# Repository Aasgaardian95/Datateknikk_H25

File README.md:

## Marius Aasgaard sin personlige GitHub

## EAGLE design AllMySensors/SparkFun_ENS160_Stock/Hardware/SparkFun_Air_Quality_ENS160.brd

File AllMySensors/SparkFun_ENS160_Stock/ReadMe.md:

SparkFun Indoor Air Quality Sensor - ENS160
========================================

[*SparkFun Indoor Air Quality Sensor-ENS160 (SEN-20844)*](https://www.sparkfun.com/products/20844)

The SparkFun ENS160 Indoor Air Quality Sensor is a digital multi-gas sensor solution with four sensor elements that can be used in a wide range of applications including building automation, smart home, and HVAC. The independent hotplate control allows the detection of volatile organic compounds (VOCs) including ethanol, toluene, hydrogen, and oxidizing gases with superior sensitivity. The ENS160 supports intelligent algorithms to process raw sensor measurements on-chip. These algorithms calculate CO2-equivalents, TVOC, air quality indices (AQIs), and perform humidity and temperature compensation, as well as baseline management, all on-chip. Raw sensor measurements can be read for further customization. 

The ENS160 from ScioSense is a digital multi-gas sensor consisting of four independent heaters and gas sensor elements based on metal oxide (MOX) technology and a controller. TrueVOC® air quality detection provides outputs such as eCO2, TVOC, and AQI in compliance with worldwide IAQ standards.

Along with the plug-and-play Qwiic connectors, both I<sup>2</sup>C and SPI functionality have been broken out to 0.1"-spaced pins in case you prefer to use a breadboard. 

**Note:** The default I<sup>2</sup>C address of the ENS160 is 0x53 and is jumper selectable to 0x52. 

Repository Contents
-------------------

* **/Documentation** - Data sheets, additional product information
* **/Hardware** - Eagle design files (.brd, .sch)
* **/Production** - Production panel files (.brd)

Documentation
--------------

* **[Fritzing Part](https://github.com/sparkfun/Fritzing_Parts/blob/main/products/20844_sfe_indoor_air_quality_sensor_ens160_qwiic_eco2_tvoc_aqi.fzpz)** - Fritzing part for the SparkFun Indoor Air Quality Sensor - ENS160.
* **[Library](https://github.com/sparkfun/SparkFun_Indoor_Air_Quality_Sensor-ENS160_Arduino_Library)** - Arduino library for the SparkFun Indoor Air Quality Sensor - ENS160.
* **[Hookup Guide](https://learn.sparkfun.com/tutorials/sparkfun-indoor-air-quality-sensor---ens160-qwiic-hookup-guide)** - Basic hookup guide for the SparkFun Indoor Air Quality Sensor - ENS160.

Product Versions
----------------
* [SEN-20844](https://www.sparkfun.com/products/20844) - v1.0

Version History
---------------
* v1.0 - Initial Release

License Information
-------------------

This product is _**open source**_! 

Please review the LICENSE.md file for license information. 

If you have any questions or concerns on licensing, please contact technical support on our [SparkFun forums](https://forum.sparkfun.com/viewforum.php?f=152).

Distributed as-is; no warranty is given.

- Your friends at SparkFun.

_<COLLABORATION CREDIT>_

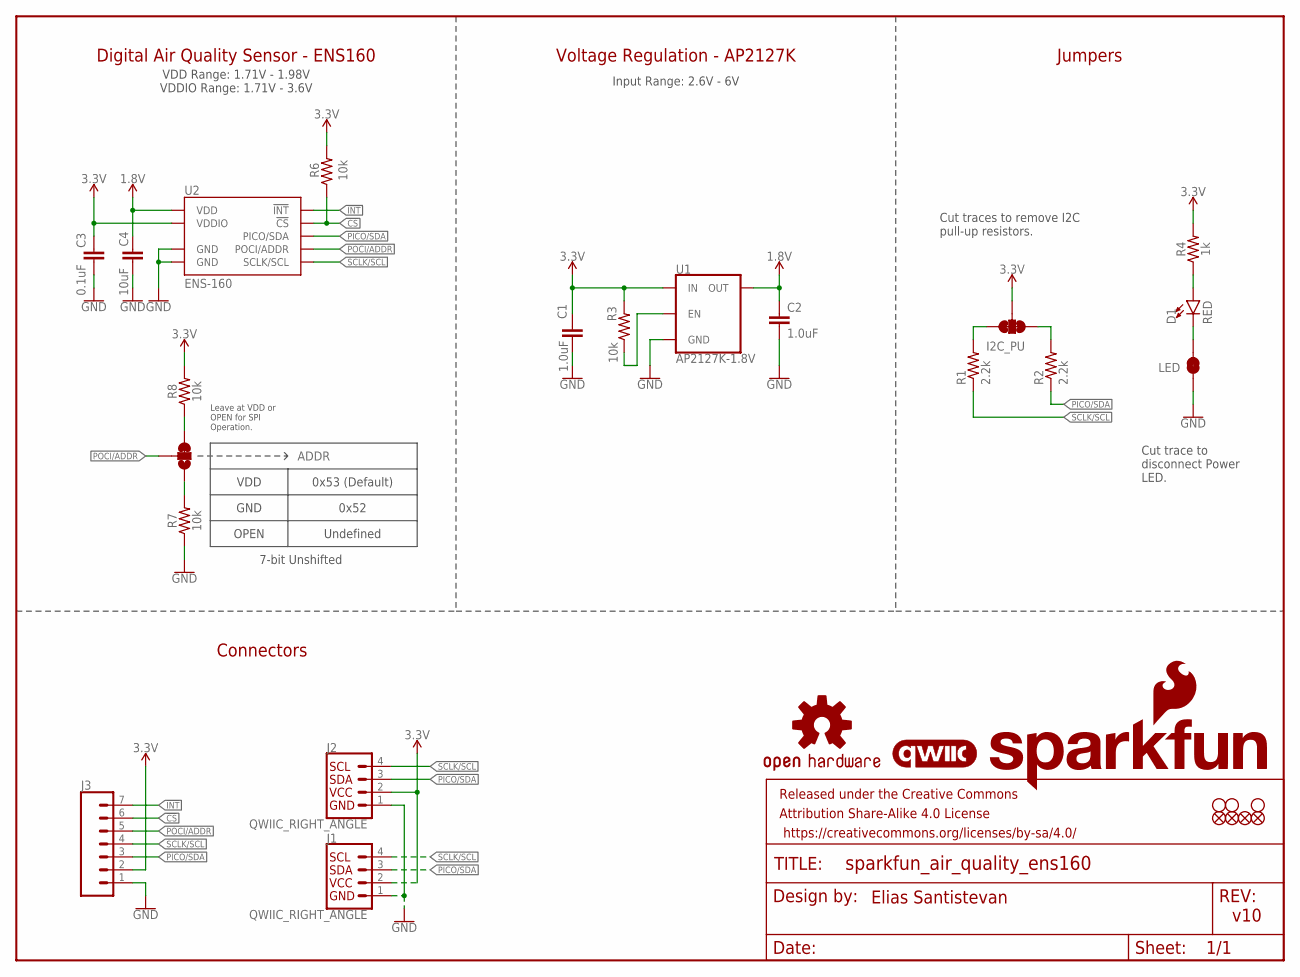
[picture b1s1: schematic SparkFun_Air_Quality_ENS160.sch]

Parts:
ADDR: JUMPER-SMT_3_1-NC_TRACE_SILK; SMT-JUMPER_3_1-NC_TRACE_SILK
C1, C2: 1.0uF; 0603
C3: 0.1uF; 0603
C4: 10uF; 0603
D1: RED; LED-0603
FD1, FD2, FD3, FD4: FIDUCIAL1X2; FIDUCIAL-1X2
FRAME1: FRAME-LETTER; CREATIVE_COMMONS
I2C_PU: S_MODE; SMT-JUMPER_3_2-NC_TRACE_SILK
J1, J2: QWIIC_RIGHT_ANGLE; JST04_1MM_RA
J3: CONN_07NO_SILK; 1X07_NO_SILK
LED: JUMPER-SMT_2_NC_TRACE_SILK; SMT-JUMPER_2_NC_TRACE_SILK
LOGO2: OSHW-LOGOMINI; OSHW-LOGO-MINI
LOGO3: SFE_LOGO_NAME_FLAME.1_INCH; SFE_LOGO_NAME_FLAME_.1
LOGO4: QWIIC_LOGO_4MM; QWIIC_4MM
R1, R2: 2.2k; 0603
R3, R6, R7, R8: 10k; 0603
R4: 1k; 0603
STANDOFF1, STANDOFF2, STANDOFF5: STAND-OFFTIGHT; STAND-OFF-TIGHT
U1: AP2127K-1.8V; SOT23-5
U2: ENS-160; LGA-9

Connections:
1.8V: C2.1, C4.1, U1.5 (OUT), U2.P4 (VDD)
3.3V: C1.1, C3.1, I2C_PU.2, J1.2, J2.2, J3.2, R3.2, R4.2, R6.2, R8.2, U1.1 (IN), U2.P5 (VDDIO)
!CS!: J3.6, R6.1, U2.P7 (!CS!)
!INT!: J3.7, U2.P6 (!INT!)
GND: C1.2, C2.2, C3.2, C4.2, J1.1, J2.1, J3.1, LED.1, R7.1, U1.2 (GND), U2.P8 (GND), U2.P9 (GND)
unnamed: R3.1, U1.3 (EN)
unnamed: D1.A, R4.1
unnamed: D1.C, LED.2
unnamed: ADDR.3, R8.1
unnamed: I2C_PU.1, R1.2
unnamed: I2C_PU.3, R2.2
unnamed: ADDR.1, R7.2
PICO/SDA: J1.3, J2.3, J3.3, R2.1, U2.P1 (PICO/SDA)
POCI/ADDR: ADDR.2, J3.5, U2.P3 (POCI/ADDR)
SCLK/SCL: J1.4, J2.4, J3.4, R1.1, U2.P2 (SCLK/SCL)

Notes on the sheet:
Cut traces to remove I2C pull-up resistors.
v10
Jumpers
Cut trace to disconnect Power LED.
Connectors
Elias Santistevan
Digital Air Quality Sensor - ENS160
VDD Range: 1.71V - 1.98V VDDIO Range: 1.71V - 3.6V
Voltage Regulation - AP2127K
VDD
GND
OPEN
0x52
0x53 (Default)
Undefined
7-bit Unshifted
Input Range: 2.6V - 6V
Leave at VDD or OPEN for SPI Operation.

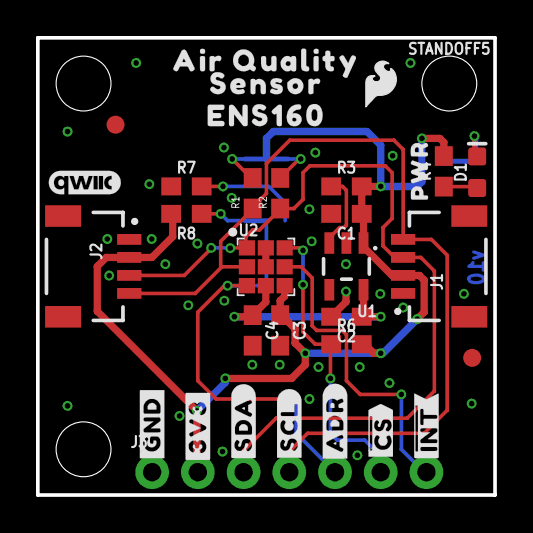
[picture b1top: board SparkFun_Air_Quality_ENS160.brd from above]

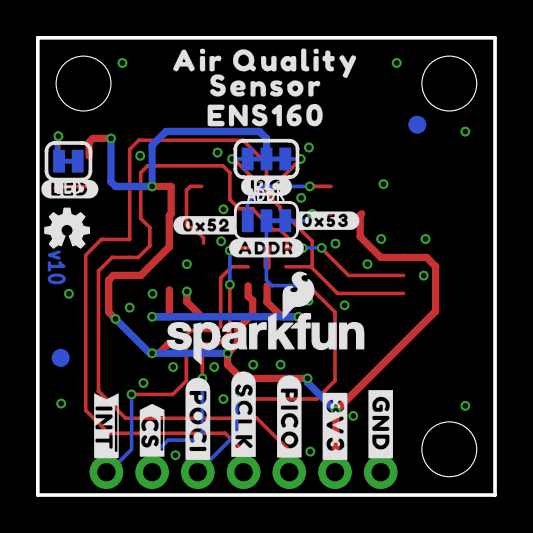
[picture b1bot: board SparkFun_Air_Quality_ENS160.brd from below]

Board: 2 copper layers, 25.4 x 25.4 mm, 58 parts (22 on the bottom side), 15 nets.

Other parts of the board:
U$1, U$9: #GND#3
U$2, U$10: #3V3#4
U$3: #SDA#5
U$4: #SCL#4
U$5, U$28: ENS16016
U$6: #ADDR#6
U$7: #SCLK#16021
U$8: #ADR#441018
U$11: ##INT##9
U$12, U$17: AIR_QUALITY441014
U$13, U$19: SENSOR441015
U$14: #0X53#16019
U$15: #0X52#16019
U$16: #LED#11
U$18: ##INT##6
U$20: SFE_LOGO_FLAME_.1
U$21: PWR9
U$22: ##CS##16019
U$23: #POCI#16020
U$24: #PICO#16021
U$25: #I2C#11
U$27: ##CS##441016

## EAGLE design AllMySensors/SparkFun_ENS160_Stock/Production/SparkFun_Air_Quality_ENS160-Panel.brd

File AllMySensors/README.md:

# Sensorbiblioteker

## Oversikt
Denne katalogen samler alle Arduino-bibliotekene som brukes i undervisningsprosjektet. Hvert bibliotek arver fra `BaseSensor` og følger samme struktur med en `src/`-mappe for kode og en `examples/`-mappe med minst ett komplett `.ino`-program. Les README-filen i hvert bibliotek for detaljert bruk, koblingsskjema og læringsmål.

## Struktur
```
.
├── BME280Sensor/
├── BaseSensor/
├── ENS160Sensor/
├── KeypadInput/
├── LDRSensor/
├── PIRSensor/
└── RFIDReader/
```

## Biblioteksliste
| Bibliotek | Formål | Eksempelfil |
| --- | --- | --- |
| `BME280Sensor` | Leser temperatur, fuktighet og trykk over I²C. | `examples/BME280Sensor_Example/BME280Sensor_Example.ino` |
| `BaseSensor` | Abstrakt grunnklasse som standardiserer `begin()`, `read()` og logging. | Brukes av alle andre biblioteker | 
| `ENS160Sensor` | Håndterer luftkvalitetssensoren ENS160 med eCO₂- og AQI-data. | `examples/ENS160Sensor_Example/ENS160Sensor_Example.ino` |
| `KeypadInput` | Leser 4x4-matrise-tastatur og leverer siste tastetrykk. | `examples/Keypad_AccessControl/Keypad_AccessControl.ino` |
| `LDRSensor` | Leser analogt lysnivå fra LDR i spenningsdeler. | `examples/LDRSensor_Example/LDRSensor_Example.ino` |
| `PIRSensor` | Registrerer bevegelse fra en PIR-sensor og styrer indikator-LED. | `examples/PIRSensor_Example/PIRSensor_Example.ino` |
| `RFIDReader` | Styrer MFRC522 RFID-leser via SPI og eksponerer kortets UID. | `examples/RFIDReader_Example/RFIDReader_Example.ino` |

## Bruk av bibliotekene
1. Kopier mappen til `Documents/Arduino/libraries/`.
2. Start Arduino IDE og åpne eksemplene fra `Fil → Eksempler → <Biblioteksnavn>`.
3. Kompiler og last opp til et kompatibelt kort (Arduino Uno, Nano o.l.).

Alle bibliotekene kan kombineres gjennom `BaseSensor`-grensesnittet for å demonstrere objektorientert design og polymorfisme.

## For undervisning
Strukturen gjør det enkelt å diskutere:
- Hvordan arv og virtuelle metoder brukes for å gi felles API til ulike sensorer.
- Forskjeller mellom analoge, digitale, I²C- og SPI-baserte sensorer.
- Hvordan komplette undervisningsopplegg kan bygges ved å kombinere flere sensorer og felles baseklasser.

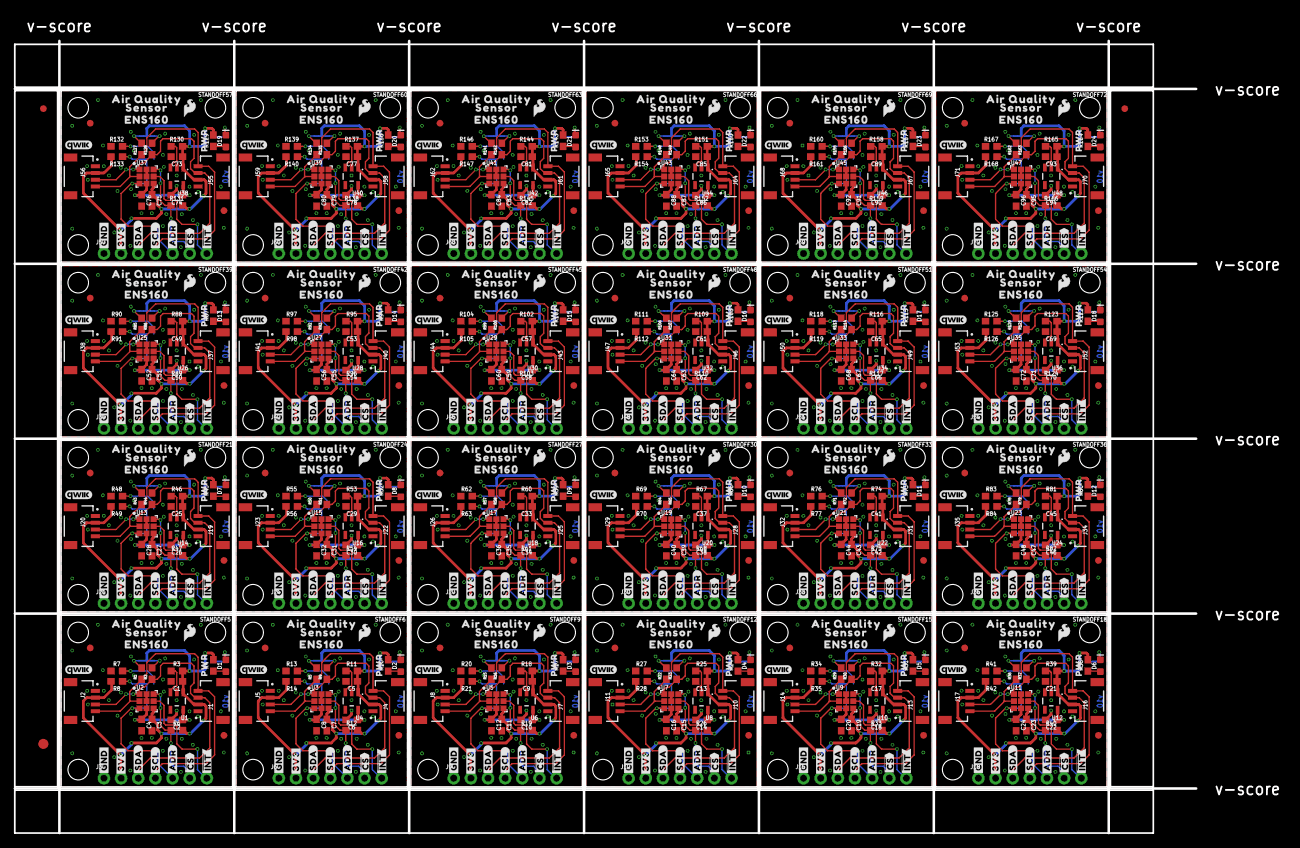
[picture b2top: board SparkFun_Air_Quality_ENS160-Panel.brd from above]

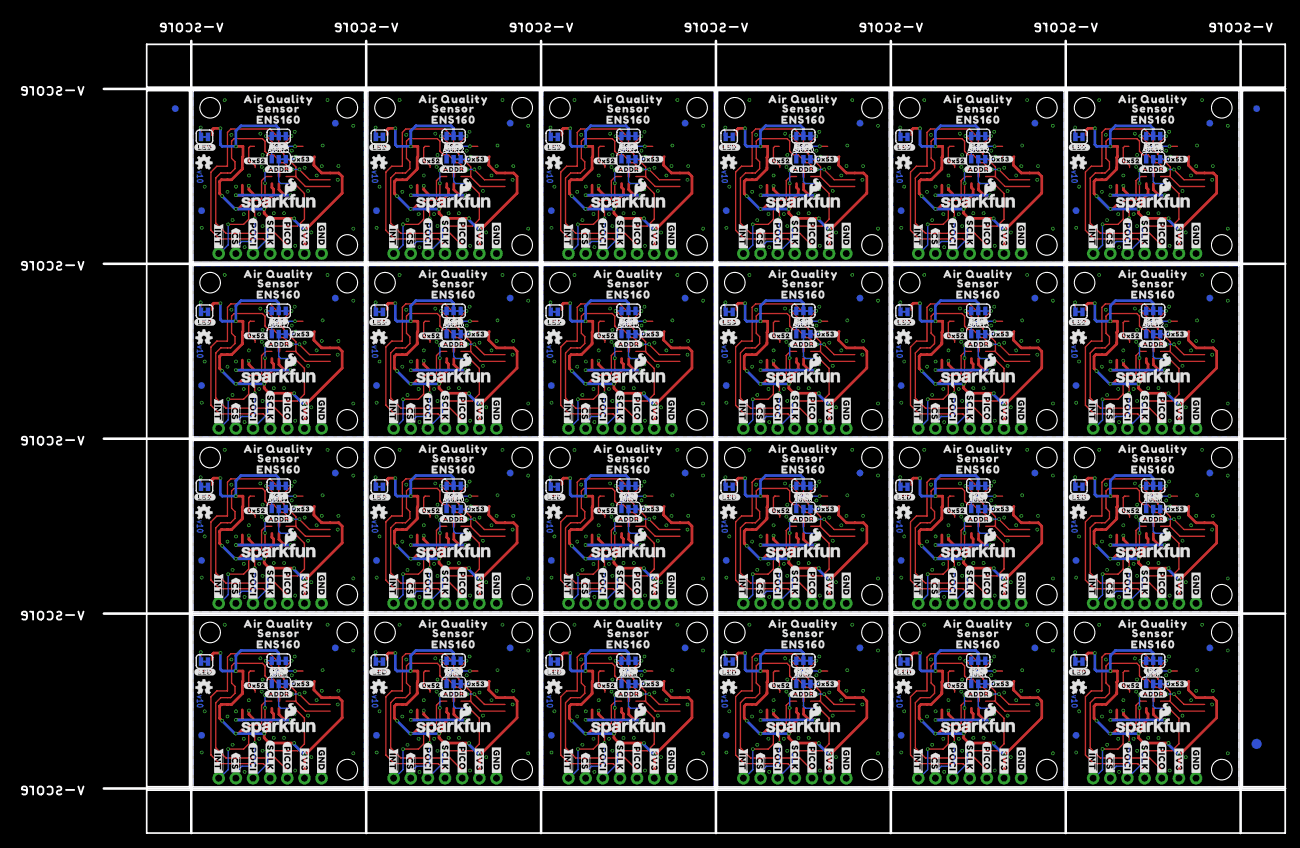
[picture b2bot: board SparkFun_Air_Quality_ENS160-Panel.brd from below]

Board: 2 copper layers, 188.2 x 121.2 mm, 1374 parts (531 on the bottom side), 360 nets.

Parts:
ADDR, ADDR1, ADDR2, ADDR3, ADDR4, ADDR5, ADDR6, ADDR7, ADDR8, ADDR9, ADDR10, ADDR11, ADDR12, ADDR13, ADDR14, ADDR15, ADDR16, ADDR17, ADDR18, ADDR19, ADDR20, ADDR21, ADDR22, ADDR23: JUMPER-SMT_3_1-NC_TRACE_SILK; SMT-JUMPER_3_1-NC_TRACE_SILK
C1, C2, C5, C6, C9, C10, C13, C14, C17, C18, C21, C22, C25, C26, C29, C30, C33, C34, C37, C38, C41, C42, C45, C46, C49, C50, C53, C54, C57, C58, C61, C62, C65, C66, C69, C70, C73, C74, C77, C78, C81, C82, C85, C86, C89, C90, C93, C94: 1.0uF; 0603
C3, C7, C11, C15, C19, C23, C27, C31, C35, C39, C43, C47, C51, C55, C59, C63, C67, C71, C75, C79, C83, C87, C91, C95: 0.1uF; 0603
C4, C8, C12, C16, C20, C24, C28, C32, C36, C40, C44, C48, C52, C56, C60, C64, C68, C72, C76, C80, C84, C88, C92, C96: 10uF; 0603
D1, D2, D3, D4, D5, D6, D7, D8, D9, D10, D11, D12, D13, D14, D15, D16, D17, D18, D19, D20, D21, D22, D23, D24: RED; LED-0603
E$1, E$2, E$3, E$4: FIDUCIAL-1X2
E$5, E$6: FIDUCIAL-1.5X3
FD1, FD2, FD3, FD4, FD5, FD6, FD7, FD8, FD9, FD10, FD11, FD12, FD13, FD14, FD15, FD16, FD17, FD18, FD19, FD20, FD21, FD22, FD23, FD24, FD25, FD26, FD27, FD28, FD29, FD30, FD31, FD32, FD33, FD34, FD35, FD36, FD37, FD38, FD39, FD40, FD41, FD42, FD43, FD44, FD45, FD46, FD47, FD48, FD49, FD50, FD51, FD52, FD53, FD54, FD55, FD56, FD57, FD58, FD59, FD60, FD61, FD62, FD63, FD64, FD65, FD66, FD67, FD68, FD69, FD70, FD71, FD72, FD73, FD74, FD75, FD76, FD77, FD78, FD79, FD80, FD81, FD82, FD83, FD84, FD85, FD86, FD87, FD88, FD89, FD90, FD91, FD92, FD93, FD94, FD95, FD96: FIDUCIAL1X2; FIDUCIAL-1X2
I2C_PU, I2C_PU1, I2C_PU2, I2C_PU3, I2C_PU4, I2C_PU5, I2C_PU6, I2C_PU7, I2C_PU8, I2C_PU9, I2C_PU10, I2C_PU11, I2C_PU12, I2C_PU13, I2C_PU14, I2C_PU15, I2C_PU16, I2C_PU17, I2C_PU18, I2C_PU19, I2C_PU20, I2C_PU21, I2C_PU22, I2C_PU23: S_MODE; SMT-JUMPER_3_2-NC_TRACE_SILK
J1, J2, J4, J5, J7, J8, J10, J11, J13, J14, J16, J17, J19, J20, J22, J23, J25, J26, J28, J29, J31, J32, J34, J35, J37, J38, J40, J41, J43, J44, J46, J47, J49, J50, J52, J53, J55, J56, J58, J59, J61, J62, J64, J65, J67, J68, J70, J71: QWIIC_RIGHT_ANGLE; JST04_1MM_RA
J3, J6, J9, J12, J15, J18, J21, J24, J27, J30, J33, J36, J39, J42, J45, J48, J51, J54, J57, J60, J63, J66, J69, J72: 1X07_NO_SILK
LED, LED1, LED2, LED3, LED4, LED5, LED6, LED7, LED8, LED9, LED10, LED11, LED12, LED13, LED14, LED15, LED16, LED17, LED18, LED19, LED20, LED21, LED22, LED23: JUMPER-SMT_2_NC_TRACE_SILK; SMT-JUMPER_2_NC_TRACE_SILK
LOGO1, LOGO2, LOGO7, LOGO10, LOGO13, LOGO16, LOGO19, LOGO22, LOGO25, LOGO28, LOGO31, LOGO34, LOGO37, LOGO40, LOGO43, LOGO46, LOGO49, LOGO52, LOGO55, LOGO58, LOGO61, LOGO64, LOGO67, LOGO70: OSHW-LOGOMINI; OSHW-LOGO-MINI
LOGO3, LOGO5, LOGO8, LOGO11, LOGO14, LOGO17, LOGO20, LOGO23, LOGO26, LOGO29, LOGO32, LOGO35, LOGO38, LOGO41, LOGO44, LOGO47, LOGO50, LOGO53, LOGO56, LOGO59, LOGO62, LOGO65, LOGO68, LOGO71: SFE_LOGO_NAME_FLAME.1_INCH; SFE_LOGO_NAME_FLAME_.1
LOGO4, LOGO6, LOGO9, LOGO12, LOGO15, LOGO18, LOGO21, LOGO24, LOGO27, LOGO30, LOGO33, LOGO36, LOGO39, LOGO42, LOGO45, LOGO48, LOGO51, LOGO54, LOGO57, LOGO60, LOGO63, LOGO66, LOGO69, LOGO72: QWIIC_LOGO_4MM; QWIIC_4MM
R1, R2, R5, R9, R15, R16, R22, R23, R29, R30, R36, R37, R43, R44, R50, R51, R57, R58, R64, R65, R71, R72, R78, R79, R85, R86, R92, R93, R99, R100, R106, R107, R113, R114, R120, R121, R127, R128, R134, R135, R141, R142, R148, R149, R155, R156, R162, R163: 2.2k; 0603
R3, R6, R7, R8, R11, R12, R13, R14, R18, R19, R20, R21, R25, R26, R27, R28, R32, R33, R34, R35, R39, R40, R41, R42, R46, R47, R48, R49, R53, R54, R55, R56, R60, R61, R62, R63, R67, R68, R69, R70, R74, R75, R76, R77, R81, R82, R83, R84, R88, R89, R90, R91, R95, R96, R97, R98, R102, R103, R104, R105, R109, R110, R111, R112, R116, R117, R118, R119, R123, R124, R125, R126, R130, R131, R132, R133, R137, R138, R139, R140, R144, R145, R146, R147, R151, R152, R153, R154, R158, R159, R160, R161, R165, R166, R167, R168: 10k; 0603
R4, R10, R17, R24, R31, R38, R45, R52, R59, R66, R73, R80, R87, R94, R101, R108, R115, R122, R129, R136, R143, R150, R157, R164: 1k; 0603
STANDOFF1, STANDOFF2, STANDOFF3, STANDOFF4, STANDOFF5, STANDOFF6, STANDOFF7, STANDOFF8, STANDOFF9, STANDOFF10, STANDOFF11, STANDOFF12, STANDOFF13, STANDOFF14, STANDOFF15, STANDOFF16, STANDOFF17, STANDOFF18, STANDOFF19, STANDOFF20, STANDOFF21, STANDOFF22, STANDOFF23, STANDOFF24, STANDOFF25, STANDOFF26, STANDOFF27, STANDOFF28, STANDOFF29, STANDOFF30, STANDOFF31, STANDOFF32, STANDOFF33, STANDOFF34, STANDOFF35, STANDOFF36, STANDOFF37, STANDOFF38, STANDOFF39, STANDOFF40, STANDOFF41, STANDOFF42, STANDOFF43, STANDOFF44, STANDOFF45, STANDOFF46, STANDOFF47, STANDOFF48, STANDOFF49, STANDOFF50, STANDOFF51, STANDOFF52, STANDOFF53, STANDOFF54, STANDOFF55, STANDOFF56, STANDOFF57, STANDOFF58, STANDOFF59, STANDOFF60, STANDOFF61, STANDOFF62, STANDOFF63, STANDOFF64, STANDOFF65, STANDOFF66, STANDOFF67, STANDOFF68, STANDOFF69, STANDOFF70, STANDOFF71, STANDOFF72: STAND-OFFTIGHT; STAND-OFF-TIGHT
U1, U4, U6, U8, U10, U12, U14, U16, U18, U20, U22, U24, U26, U28, U30, U32, U34, U36, U38, U40, U42, U44, U46, U48: AP2127K-1.8V; SOT23-5
U2, U3, U5, U7, U9, U11, U13, U15, U17, U19, U21, U23, U25, U27, U29, U31, U33, U35, U37, U39, U41, U43, U45, U47: ENS-160; LGA-9
U$1, U$9, U$30, U$34, U$57, U$61, U$84, U$88, U$111, U$115, U$138, U$142, U$165, U$169, U$192, U$196, U$219, U$223, U$246, U$250, U$273, U$277, U$300, U$304, U$327, U$331, U$354, U$358, U$381, U$385, U$408, U$412, U$435, U$439, U$462, U$466, U$489, U$493, U$516, U$520, U$543, U$547, U$570, U$574, U$597, U$601, U$624, U$628: #GND#3
U$2, U$10, U$31, U$35, U$58, U$62, U$85, U$89, U$112, U$116, U$139, U$143, U$166, U$170, U$193, U$197, U$220, U$224, U$247, U$251, U$274, U$278, U$301, U$305, U$328, U$332, U$355, U$359, U$382, U$386, U$409, U$413, U$436, U$440, U$463, U$467, U$490, U$494, U$517, U$521, U$544, U$548, U$571, U$575, U$598, U$602, U$625, U$629: #3V3#4
U$3, U$32, U$59, U$86, U$113, U$140, U$167, U$194, U$221, U$248, U$275, U$302, U$329, U$356, U$383, U$410, U$437, U$464, U$491, U$518, U$545, U$572, U$599, U$626: #SDA#5
U$4, U$33, U$60, U$87, U$114, U$141, U$168, U$195, U$222, U$249, U$276, U$303, U$330, U$357, U$384, U$411, U$438, U$465, U$492, U$519, U$546, U$573, U$600, U$627: #SCL#4
U$5, U$28, U$44, U$51, U$71, U$78, U$98, U$105, U$125, U$132, U$152, U$159, U$179, U$186, U$206, U$213, U$233, U$240, U$260, U$267, U$287, U$294, U$314, U$321, U$341, U$348, U$368, U$375, U$395, U$402, U$422, U$429, U$449, U$456, U$476, U$483, U$503, U$510, U$530, U$537, U$557, U$564, U$584, U$591, U$611, U$618, U$638, U$645: ENS16016
U$6, U$45, U$72, U$99, U$126, U$153, U$180, U$207, U$234, U$261, U$288, U$315, U$342, U$369, U$396, U$423, U$450, U$477, U$504, U$531, U$558, U$585, U$612, U$639: #ADDR#6
U$7, U$49, U$76, U$103, U$130, U$157, U$184, U$211, U$238, U$265, U$292, U$319, U$346, U$373, U$400, U$427, U$454, U$481, U$508, U$535, U$562, U$589, U$616, U$643: #SCLK#16021
U$8, U$52, U$79, U$106, U$133, U$160, U$187, U$214, U$241, U$268, U$295, U$322, U$349, U$376, U$403, U$430, U$457, U$484, U$511, U$538, U$565, U$592, U$619, U$646: #ADR#441018
U$11, U$37, U$64, U$91, U$118, U$145, U$172, U$199, U$226, U$253, U$280, U$307, U$334, U$361, U$388, U$415, U$442, U$469, U$496, U$523, U$550, U$577, U$604, U$631: ##INT##9
U$12, U$17, U$38, U$40, U$65, U$67, U$92, U$94, U$119, U$121, U$146, U$148, U$173, U$175, U$200, U$202, U$227, U$229, U$254, U$256, U$281, U$283, U$308, U$310, U$335, U$337, U$362, U$364, U$389, U$391, U$416, U$418, U$443, U$445, U$470, U$472, U$497, U$499, U$524, U$526, U$551, U$553, U$578, U$580, U$605, U$607, U$632, U$634: AIR_QUALITY441014
U$13, U$19, U$39, U$41, U$66, U$68, U$93, U$95, U$120, U$122, U$147, U$149, U$174, U$176, U$201, U$203, U$228, U$230, U$255, U$257, U$282, U$284, U$309, U$311, U$336, U$338, U$363, U$365, U$390, U$392, U$417, U$419, U$444, U$446, U$471, U$473, U$498, U$500, U$525, U$527, U$552, U$554, U$579, U$581, U$606, U$608, U$633, U$635: SENSOR441015
U$14, U$46, U$73, U$100, U$127, U$154, U$181, U$208, U$235, U$262, U$289, U$316, U$343, U$370, U$397, U$424, U$451, U$478, U$505, U$532, U$559, U$586, U$613, U$640: #0X53#16019
U$15, U$47, U$74, U$101, U$128, U$155, U$182, U$209, U$236, U$263, U$290, U$317, U$344, U$371, U$398, U$425, U$452, U$479, U$506, U$533, U$560, U$587, U$614, U$641: #0X52#16019
U$16, U$26, U$55, U$82, U$109, U$136, U$163, U$190, U$217, U$244, U$271, U$298, U$325, U$352, U$379, U$406, U$433, U$460, U$487, U$514, U$541, U$568, U$595, U$622: #LED#11
U$18, U$36, U$63, U$90, U$117, U$144, U$171, U$198, U$225, U$252, U$279, U$306, U$333, U$360, U$387, U$414, U$441, U$468, U$495, U$522, U$549, U$576, U$603, U$630: ##INT##6
U$20, U$42, U$69, U$96, U$123, U$150, U$177, U$204, U$231, U$258, U$285, U$312, U$339, U$366, U$393, U$420, U$447, U$474, U$501, U$528, U$555, U$582, U$609, U$636: SFE_LOGO_FLAME_.1
U$21, U$43, U$70, U$97, U$124, U$151, U$178, U$205, U$232, U$259, U$286, U$313, U$340, U$367, U$394, U$421, U$448, U$475, U$502, U$529, U$556, U$583, U$610, U$637: PWR9
U$22, U$48, U$75, U$102, U$129, U$156, U$183, U$210, U$237, U$264, U$291, U$318, U$345, U$372, U$399, U$426, U$453, U$480, U$507, U$534, U$561, U$588, U$615, U$642: ##CS##16019
U$23, U$53, U$80, U$107, U$134, U$161, U$188, U$215, U$242, U$269, U$296, U$323, U$350, U$377, U$404, U$431, U$458, U$485, U$512, U$539, U$566, U$593, U$620, U$647: #POCI#16020
U$24, U$54, U$81, U$108, U$135, U$162, U$189, U$216, U$243, U$270, U$297, U$324, U$351, U$378, U$405, U$432, U$459, U$486, U$513, U$540, U$567, U$594, U$621, U$648: #PICO#16021
U$25, U$29, U$56, U$83, U$110, U$137, U$164, U$191, U$218, U$245, U$272, U$299, U$326, U$353, U$380, U$407, U$434, U$461, U$488, U$515, U$542, U$569, U$596, U$623: #I2C#11
U$27, U$50, U$77, U$104, U$131, U$158, U$185, U$212, U$239, U$266, U$293, U$320, U$347, U$374, U$401, U$428, U$455, U$482, U$509, U$536, U$563, U$590, U$617, U$644: ##CS##441016

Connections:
1.8V: C2.1, C4.1, U1.5, U2.P4
1.8V1: C6.1, C8.1, U3.P4, U4.5
1.8V2: C10.1, C12.1, U5.P4, U6.5
1.8V3: C14.1, C16.1, U7.P4, U8.5
1.8V4: C18.1, C20.1, U9.P4, U10.5
1.8V5: C22.1, C24.1, U11.P4, U12.5
1.8V6: C26.1, C28.1, U13.P4, U14.5
1.8V7: C30.1, C32.1, U15.P4, U16.5
1.8V8: C34.1, C36.1, U17.P4, U18.5
1.8V9: C38.1, C40.1, U19.P4, U20.5
1.8V10: C42.1, C44.1, U21.P4, U22.5
1.8V11: C46.1, C48.1, U23.P4, U24.5
1.8V12: C50.1, C52.1, U25.P4, U26.5
1.8V13: C54.1, C56.1, U27.P4, U28.5
1.8V14: C58.1, C60.1, U29.P4, U30.5
1.8V15: C62.1, C64.1, U31.P4, U32.5
1.8V16: C66.1, C68.1, U33.P4, U34.5
1.8V17: C70.1, C72.1, U35.P4, U36.5
1.8V18: C74.1, C76.1, U37.P4, U38.5
1.8V19: C78.1, C80.1, U39.P4, U40.5
1.8V20: C82.1, C84.1, U41.P4, U42.5
1.8V21: C86.1, C88.1, U43.P4, U44.5
1.8V22: C90.1, C92.1, U45.P4, U46.5
1.8V23: C94.1, C96.1, U47.P4, U48.5
3.3V: C1.1, C3.1, I2C_PU.2, J1.2, J2.2, J3.2, R3.2, R4.2, R6.2, R8.2, U1.1, U2.P5
3.3V1: C5.1, C7.1, I2C_PU1.2, J4.2, J5.2, J6.2, R10.2, R11.2, R12.2, R14.2, U3.P5, U4.1
3.3V2: C9.1, C11.1, I2C_PU2.2, J7.2, J8.2, J9.2, R17.2, R18.2, R19.2, R21.2, U5.P5, U6.1
3.3V3: C13.1, C15.1, I2C_PU3.2, J10.2, J11.2, J12.2, R24.2, R25.2, R26.2, R28.2, U7.P5, U8.1
3.3V4: C17.1, C19.1, I2C_PU4.2, J13.2, J14.2, J15.2, R31.2, R32.2, R33.2, R35.2, U9.P5, U10.1
3.3V5: C21.1, C23.1, I2C_PU5.2, J16.2, J17.2, J18.2, R38.2, R39.2, R40.2, R42.2, U11.P5, U12.1
3.3V6: C25.1, C27.1, I2C_PU6.2, J19.2, J20.2, J21.2, R45.2, R46.2, R47.2, R49.2, U13.P5, U14.1
3.3V7: C29.1, C31.1, I2C_PU7.2, J22.2, J23.2, J24.2, R52.2, R53.2, R54.2, R56.2, U15.P5, U16.1
3.3V8: C33.1, C35.1, I2C_PU8.2, J25.2, J26.2, J27.2, R59.2, R60.2, R61.2, R63.2, U17.P5, U18.1
3.3V9: C37.1, C39.1, I2C_PU9.2, J28.2, J29.2, J30.2, R66.2, R67.2, R68.2, R70.2, U19.P5, U20.1
3.3V10: C41.1, C43.1, I2C_PU10.2, J31.2, J32.2, J33.2, R73.2, R74.2, R75.2, R77.2, U21.P5, U22.1
3.3V11: C45.1, C47.1, I2C_PU11.2, J34.2, J35.2, J36.2, R80.2, R81.2, R82.2, R84.2, U23.P5, U24.1
3.3V12: C49.1, C51.1, I2C_PU12.2, J37.2, J38.2, J39.2, R87.2, R88.2, R89.2, R91.2, U25.P5, U26.1
3.3V13: C53.1, C55.1, I2C_PU13.2, J40.2, J41.2, J42.2, R94.2, R95.2, R96.2, R98.2, U27.P5, U28.1
3.3V14: C57.1, C59.1, I2C_PU14.2, J43.2, J44.2, J45.2, R101.2, R102.2, R103.2, R105.2, U29.P5, U30.1
3.3V15: C61.1, C63.1, I2C_PU15.2, J46.2, J47.2, J48.2, R108.2, R109.2, R110.2, R112.2, U31.P5, U32.1
3.3V16: C65.1, C67.1, I2C_PU16.2, J49.2, J50.2, J51.2, R115.2, R116.2, R117.2, R119.2, U33.P5, U34.1
3.3V17: C69.1, C71.1, I2C_PU17.2, J52.2, J53.2, J54.2, R122.2, R123.2, R124.2, R126.2, U35.P5, U36.1
3.3V18: C73.1, C75.1, I2C_PU18.2, J55.2, J56.2, J57.2, R129.2, R130.2, R131.2, R133.2, U37.P5, U38.1
3.3V19: C77.1, C79.1, I2C_PU19.2, J58.2, J59.2, J60.2, R136.2, R137.2, R138.2, R140.2, U39.P5, U40.1
3.3V20: C81.1, C83.1, I2C_PU20.2, J61.2, J62.2, J63.2, R143.2, R144.2, R145.2, R147.2, U41.P5, U42.1
3.3V21: C85.1, C87.1, I2C_PU21.2, J64.2, J65.2, J66.2, R150.2, R151.2, R152.2, R154.2, U43.P5, U44.1
3.3V22: C89.1, C91.1, I2C_PU22.2, J67.2, J68.2, J69.2, R157.2, R158.2, R159.2, R161.2, U45.P5, U46.1
3.3V23: C93.1, C95.1, I2C_PU23.2, J70.2, J71.2, J72.2, R164.2, R165.2, R166.2, R168.2, U47.P5, U48.1
!CS!: J3.6, R6.1, U2.P7
!CS!1: J6.6, R12.1, U3.P7
!CS!2: J9.6, R19.1, U5.P7
!CS!3: J12.6, R26.1, U7.P7
!CS!4: J15.6, R33.1, U9.P7
!CS!5: J18.6, R40.1, U11.P7
!CS!6: J21.6, R47.1, U13.P7
!CS!7: J24.6, R54.1, U15.P7
!CS!8: J27.6, R61.1, U17.P7
!CS!9: J30.6, R68.1, U19.P7
!CS!10: J33.6, R75.1, U21.P7
!CS!11: J36.6, R82.1, U23.P7
!CS!12: J39.6, R89.1, U25.P7
!CS!13: J42.6, R96.1, U27.P7
!CS!14: J45.6, R103.1, U29.P7
!CS!15: J48.6, R110.1, U31.P7
!CS!16: J51.6, R117.1, U33.P7
!CS!17: J54.6, R124.1, U35.P7
!CS!18: J57.6, R131.1, U37.P7
!CS!19: J60.6, R138.1, U39.P7
!CS!20: J63.6, R145.1, U41.P7
!CS!21: J66.6, R152.1, U43.P7
!CS!22: J69.6, R159.1, U45.P7
!CS!23: J72.6, R166.1, U47.P7
!INT!: J3.7, U2.P6
!INT!1: J6.7, U3.P6
!INT!2: J9.7, U5.P6
!INT!3: J12.7, U7.P6
!INT!4: J15.7, U9.P6
!INT!5: J18.7, U11.P6
!INT!6: J21.7, U13.P6
!INT!7: J24.7, U15.P6
!INT!8: J27.7, U17.P6
!INT!9: J30.7, U19.P6
!INT!10: J33.7, U21.P6
!INT!11: J36.7, U23.P6
!INT!12: J39.7, U25.P6
!INT!13: J42.7, U27.P6
!INT!14: J45.7, U29.P6
!INT!15: J48.7, U31.P6
!INT!16: J51.7, U33.P6
!INT!17: J54.7, U35.P6
!INT!18: J57.7, U37.P6
!INT!19: J60.7, U39.P6
!INT!20: J63.7, U41.P6
!INT!21: J66.7, U43.P6
!INT!22: J69.7, U45.P6
!INT!23: J72.7, U47.P6
GND: C1.2, C2.2, C3.2, C4.2, J1.1, J2.1, J3.1, LED.1, R7.1, U1.2, U2.P8, U2.P9
GND1: C5.2, C6.2, C7.2, C8.2, J4.1, J5.1, J6.1, LED1.1, R13.1, U3.P8, U3.P9, U4.2
GND2: C9.2, C10.2, C11.2, C12.2, J7.1, J8.1, J9.1, LED2.1, R20.1, U5.P8, U5.P9, U6.2
GND3: C13.2, C14.2, C15.2, C16.2, J10.1, J11.1, J12.1, LED3.1, R27.1, U7.P8, U7.P9, U8.2
GND4: C17.2, C18.2, C19.2, C20.2, J13.1, J14.1, J15.1, LED4.1, R34.1, U9.P8, U9.P9, U10.2
GND5: C21.2, C22.2, C23.2, C24.2, J16.1, J17.1, J18.1, LED5.1, R41.1, U11.P8, U11.P9, U12.2
GND6: C25.2, C26.2, C27.2, C28.2, J19.1, J20.1, J21.1, LED6.1, R48.1, U13.P8, U13.P9, U14.2
GND7: C29.2, C30.2, C31.2, C32.2, J22.1, J23.1, J24.1, LED7.1, R55.1, U15.P8, U15.P9, U16.2
GND8: C33.2, C34.2, C35.2, C36.2, J25.1, J26.1, J27.1, LED8.1, R62.1, U17.P8, U17.P9, U18.2
GND9: C37.2, C38.2, C39.2, C40.2, J28.1, J29.1, J30.1, LED9.1, R69.1, U19.P8, U19.P9, U20.2
GND10: C41.2, C42.2, C43.2, C44.2, J31.1, J32.1, J33.1, LED10.1, R76.1, U21.P8, U21.P9, U22.2
GND11: C45.2, C46.2, C47.2, C48.2, J34.1, J35.1, J36.1, LED11.1, R83.1, U23.P8, U23.P9, U24.2
GND12: C49.2, C50.2, C51.2, C52.2, J37.1, J38.1, J39.1, LED12.1, R90.1, U25.P8, U25.P9, U26.2
GND13: C53.2, C54.2, C55.2, C56.2, J40.1, J41.1, J42.1, LED13.1, R97.1, U27.P8, U27.P9, U28.2
GND14: C57.2, C58.2, C59.2, C60.2, J43.1, J44.1, J45.1, LED14.1, R104.1, U29.P8, U29.P9, U30.2
GND15: C61.2, C62.2, C63.2, C64.2, J46.1, J47.1, J48.1, LED15.1, R111.1, U31.P8, U31.P9, U32.2
GND16: C65.2, C66.2, C67.2, C68.2, J49.1, J50.1, J51.1, LED16.1, R118.1, U33.P8, U33.P9, U34.2
GND17: C69.2, C70.2, C71.2, C72.2, J52.1, J53.1, J54.1, LED17.1, R125.1, U35.P8, U35.P9, U36.2
GND18: C73.2, C74.2, C75.2, C76.2, J55.1, J56.1, J57.1, LED18.1, R132.1, U37.P8, U37.P9, U38.2
GND19: C77.2, C78.2, C79.2, C80.2, J58.1, J59.1, J60.1, LED19.1, R139.1, U39.P8, U39.P9, U40.2
GND20: C81.2, C82.2, C83.2, C84.2, J61.1, J62.1, J63.1, LED20.1, R146.1, U41.P8, U41.P9, U42.2
GND21: C85.2, C86.2, C87.2, C88.2, J64.1, J65.1, J66.1, LED21.1, R153.1, U43.P8, U43.P9, U44.2
GND22: C89.2, C90.2, C91.2, C92.2, J67.1, J68.1, J69.1, LED22.1, R160.1, U45.P8, U45.P9, U46.2
GND23: C93.2, C94.2, C95.2, C96.2, J70.1, J71.1, J72.1, LED23.1, R167.1, U47.P8, U47.P9, U48.2
unnamed: R3.1, U1.3
unnamed: D1.A, R4.1
unnamed: D1.C, LED.2
unnamed: ADDR.3, R8.1
unnamed: I2C_PU.1, R1.2
unnamed: I2C_PU.3, R2.2
unnamed: ADDR.1, R7.2
unnamed: I2C_PU1.1, R5.2
unnamed: I2C_PU1.3, R9.2
unnamed: D2.A, R10.1
unnamed: D2.C, LED1.2
unnamed: R11.1, U4.3
unnamed: ADDR1.3, R14.1
unnamed: ADDR1.1, R13.2
unnamed: I2C_PU2.1, R15.2
unnamed: I2C_PU2.3, R16.2
unnamed: D3.A, R17.1
unnamed: D3.C, LED2.2
unnamed: R18.1, U6.3
unnamed: ADDR2.3, R21.1
unnamed: ADDR2.1, R20.2
unnamed: I2C_PU3.1, R22.2
unnamed: I2C_PU3.3, R23.2
unnamed: D4.A, R24.1
unnamed: D4.C, LED3.2
unnamed: R25.1, U8.3
unnamed: ADDR3.3, R28.1
unnamed: ADDR3.1, R27.2
unnamed: I2C_PU4.1, R29.2
unnamed: I2C_PU4.3, R30.2
unnamed: D5.A, R31.1
unnamed: D5.C, LED4.2
unnamed: R32.1, U10.3
unnamed: ADDR4.3, R35.1
unnamed: ADDR4.1, R34.2
unnamed: I2C_PU5.1, R36.2
unnamed: I2C_PU5.3, R37.2
unnamed: D6.A, R38.1
unnamed: D6.C, LED5.2
unnamed: R39.1, U12.3
unnamed: ADDR5.3, R42.1
unnamed: ADDR5.1, R41.2
unnamed: I2C_PU6.1, R43.2
unnamed: I2C_PU6.3, R44.2
unnamed: D7.A, R45.1
unnamed: D7.C, LED6.2
unnamed: R46.1, U14.3
unnamed: ADDR6.3, R49.1
unnamed: ADDR6.1, R48.2
unnamed: I2C_PU7.1, R50.2
unnamed: I2C_PU7.3, R51.2
unnamed: D8.A, R52.1
unnamed: D8.C, LED7.2
unnamed: R53.1, U16.3
unnamed: ADDR7.3, R56.1
unnamed: ADDR7.1, R55.2
unnamed: I2C_PU8.1, R57.2
unnamed: I2C_PU8.3, R58.2
unnamed: D9.A, R59.1
unnamed: D9.C, LED8.2
unnamed: R60.1, U18.3
unnamed: ADDR8.3, R63.1
unnamed: ADDR8.1, R62.2
unnamed: I2C_PU9.1, R64.2
unnamed: I2C_PU9.3, R65.2
unnamed: D10.A, R66.1
unnamed: D10.C, LED9.2
unnamed: R67.1, U20.3
unnamed: ADDR9.3, R70.1
unnamed: ADDR9.1, R69.2
unnamed: I2C_PU10.1, R71.2
unnamed: I2C_PU10.3, R72.2
unnamed: D11.A, R73.1
unnamed: D11.C, LED10.2
unnamed: R74.1, U22.3
unnamed: ADDR10.3, R77.1
unnamed: ADDR10.1, R76.2
unnamed: I2C_PU11.1, R78.2
unnamed: I2C_PU11.3, R79.2
unnamed: D12.A, R80.1
unnamed: D12.C, LED11.2
unnamed: R81.1, U24.3
unnamed: ADDR11.3, R84.1
unnamed: ADDR11.1, R83.2
unnamed: I2C_PU12.1, R85.2
unnamed: I2C_PU12.3, R86.2
unnamed: D13.A, R87.1
unnamed: D13.C, LED12.2
unnamed: R88.1, U26.3
unnamed: ADDR12.3, R91.1
unnamed: ADDR12.1, R90.2
unnamed: I2C_PU13.1, R92.2
unnamed: I2C_PU13.3, R93.2
unnamed: D14.A, R94.1
unnamed: D14.C, LED13.2
unnamed: R95.1, U28.3
unnamed: ADDR13.3, R98.1
unnamed: ADDR13.1, R97.2
unnamed: I2C_PU14.1, R99.2
unnamed: I2C_PU14.3, R100.2
unnamed: D15.A, R101.1
unnamed: D15.C, LED14.2
unnamed: R102.1, U30.3
unnamed: ADDR14.3, R105.1
unnamed: ADDR14.1, R104.2
unnamed: I2C_PU15.1, R106.2
unnamed: I2C_PU15.3, R107.2
unnamed: D16.A, R108.1
unnamed: D16.C, LED15.2
unnamed: R109.1, U32.3
unnamed: ADDR15.3, R112.1
unnamed: ADDR15.1, R111.2
unnamed: I2C_PU16.1, R113.2
unnamed: I2C_PU16.3, R114.2
unnamed: D17.A, R115.1
unnamed: D17.C, LED16.2
unnamed: R116.1, U34.3
unnamed: ADDR16.3, R119.1
unnamed: ADDR16.1, R118.2
unnamed: I2C_PU17.1, R120.2
unnamed: I2C_PU17.3, R121.2
unnamed: D18.A, R122.1
unnamed: D18.C, LED17.2
unnamed: R123.1, U36.3
unnamed: ADDR17.3, R126.1
unnamed: ADDR17.1, R125.2
unnamed: I2C_PU18.1, R127.2
unnamed: I2C_PU18.3, R128.2
unnamed: D19.A, R129.1
unnamed: D19.C, LED18.2
unnamed: R130.1, U38.3
unnamed: ADDR18.3, R133.1
unnamed: ADDR18.1, R132.2
unnamed: I2C_PU19.1, R134.2
unnamed: I2C_PU19.3, R135.2
unnamed: D20.A, R136.1
unnamed: D20.C, LED19.2
unnamed: R137.1, U40.3
unnamed: ADDR19.3, R140.1
unnamed: ADDR19.1, R139.2
unnamed: I2C_PU20.1, R141.2
unnamed: I2C_PU20.3, R142.2
unnamed: D21.A, R143.1
unnamed: D21.C, LED20.2
unnamed: R144.1, U42.3
unnamed: ADDR20.3, R147.1
unnamed: ADDR20.1, R146.2
unnamed: I2C_PU21.1, R148.2
unnamed: I2C_PU21.3, R149.2
unnamed: D22.A, R150.1
unnamed: D22.C, LED21.2
unnamed: R151.1, U44.3
unnamed: ADDR21.3, R154.1
unnamed: ADDR21.1, R153.2
unnamed: I2C_PU22.1, R155.2
unnamed: I2C_PU22.3, R156.2
unnamed: D23.A, R157.1
unnamed: D23.C, LED22.2
unnamed: R158.1, U46.3
unnamed: ADDR22.3, R161.1
unnamed: ADDR22.1, R160.2
unnamed: I2C_PU23.1, R162.2
unnamed: I2C_PU23.3, R163.2
unnamed: D24.A, R164.1
unnamed: D24.C, LED23.2
unnamed: R165.1, U48.3
unnamed: ADDR23.3, R168.1
unnamed: ADDR23.1, R167.2
PICO/SDA: J1.3, J2.3, J3.3, R2.1, U2.P1
PICO/SDA1: J4.3, J5.3, J6.3, R9.1, U3.P1
PICO/SDA2: J7.3, J8.3, J9.3, R16.1, U5.P1
PICO/SDA3: J10.3, J11.3, J12.3, R23.1, U7.P1
PICO/SDA4: J13.3, J14.3, J15.3, R30.1, U9.P1
PICO/SDA5: J16.3, J17.3, J18.3, R37.1, U11.P1
PICO/SDA6: J19.3, J20.3, J21.3, R44.1, U13.P1
PICO/SDA7: J22.3, J23.3, J24.3, R51.1, U15.P1
PICO/SDA8: J25.3, J26.3, J27.3, R58.1, U17.P1
PICO/SDA9: J28.3, J29.3, J30.3, R65.1, U19.P1
PICO/SDA10: J31.3, J32.3, J33.3, R72.1, U21.P1
PICO/SDA11: J34.3, J35.3, J36.3, R79.1, U23.P1
PICO/SDA12: J37.3, J38.3, J39.3, R86.1, U25.P1
PICO/SDA13: J40.3, J41.3, J42.3, R93.1, U27.P1
PICO/SDA14: J43.3, J44.3, J45.3, R100.1, U29.P1
PICO/SDA15: J46.3, J47.3, J48.3, R107.1, U31.P1
PICO/SDA16: J49.3, J50.3, J51.3, R114.1, U33.P1
PICO/SDA17: J52.3, J53.3, J54.3, R121.1, U35.P1
PICO/SDA18: J55.3, J56.3, J57.3, R128.1, U37.P1
PICO/SDA19: J58.3, J59.3, J60.3, R135.1, U39.P1
PICO/SDA20: J61.3, J62.3, J63.3, R142.1, U41.P1
PICO/SDA21: J64.3, J65.3, J66.3, R149.1, U43.P1
PICO/SDA22: J67.3, J68.3, J69.3, R156.1, U45.P1
PICO/SDA23: J70.3, J71.3, J72.3, R163.1, U47.P1
POCI/ADDR: ADDR.2, J3.5, U2.P3
POCI/ADDR1: ADDR1.2, J6.5, U3.P3
POCI/ADDR2: ADDR2.2, J9.5, U5.P3
POCI/ADDR3: ADDR3.2, J12.5, U7.P3
POCI/ADDR4: ADDR4.2, J15.5, U9.P3
POCI/ADDR5: ADDR5.2, J18.5, U11.P3
POCI/ADDR6: ADDR6.2, J21.5, U13.P3
POCI/ADDR7: ADDR7.2, J24.5, U15.P3
POCI/ADDR8: ADDR8.2, J27.5, U17.P3
POCI/ADDR9: ADDR9.2, J30.5, U19.P3
POCI/ADDR10: ADDR10.2, J33.5, U21.P3
POCI/ADDR11: ADDR11.2, J36.5, U23.P3
POCI/ADDR12: ADDR12.2, J39.5, U25.P3
POCI/ADDR13: ADDR13.2, J42.5, U27.P3
POCI/ADDR14: ADDR14.2, J45.5, U29.P3
POCI/ADDR15: ADDR15.2, J48.5, U31.P3
POCI/ADDR16: ADDR16.2, J51.5, U33.P3
POCI/ADDR17: ADDR17.2, J54.5, U35.P3
POCI/ADDR18: ADDR18.2, J57.5, U37.P3
POCI/ADDR19: ADDR19.2, J60.5, U39.P3
POCI/ADDR20: ADDR20.2, J63.5, U41.P3
POCI/ADDR21: ADDR21.2, J66.5, U43.P3
POCI/ADDR22: ADDR22.2, J69.5, U45.P3
POCI/ADDR23: ADDR23.2, J72.5, U47.P3
SCLK/SCL: J1.4, J2.4, J3.4, R1.1, U2.P2
SCLK/SCL1: J4.4, J5.4, J6.4, R5.1, U3.P2
SCLK/SCL2: J7.4, J8.4, J9.4, R15.1, U5.P2
SCLK/SCL3: J10.4, J11.4, J12.4, R22.1, U7.P2
SCLK/SCL4: J13.4, J14.4, J15.4, R29.1, U9.P2
SCLK/SCL5: J16.4, J17.4, J18.4, R36.1, U11.P2
SCLK/SCL6: J19.4, J20.4, J21.4, R43.1, U13.P2
SCLK/SCL7: J22.4, J23.4, J24.4, R50.1, U15.P2
SCLK/SCL8: J25.4, J26.4, J27.4, R57.1, U17.P2
SCLK/SCL9: J28.4, J29.4, J30.4, R64.1, U19.P2
SCLK/SCL10: J31.4, J32.4, J33.4, R71.1, U21.P2
SCLK/SCL11: J34.4, J35.4, J36.4, R78.1, U23.P2
SCLK/SCL12: J37.4, J38.4, J39.4, R85.1, U25.P2
SCLK/SCL13: J40.4, J41.4, J42.4, R92.1, U27.P2
SCLK/SCL14: J43.4, J44.4, J45.4, R99.1, U29.P2
SCLK/SCL15: J46.4, J47.4, J48.4, R106.1, U31.P2
SCLK/SCL16: J49.4, J50.4, J51.4, R113.1, U33.P2
SCLK/SCL17: J52.4, J53.4, J54.4, R120.1, U35.P2
SCLK/SCL18: J55.4, J56.4, J57.4, R127.1, U37.P2
SCLK/SCL19: J58.4, J59.4, J60.4, R134.1, U39.P2
SCLK/SCL20: J61.4, J62.4, J63.4, R141.1, U41.P2
SCLK/SCL21: J64.4, J65.4, J66.4, R148.1, U43.P2
SCLK/SCL22: J67.4, J68.4, J69.4, R155.1, U45.P2
SCLK/SCL23: J70.4, J71.4, J72.4, R162.1, U47.P2

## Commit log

2025-11-06 Add README guide for customizing sensors
2025-11-06 Oppdater README-filer for sensorbibliotekene
2025-11-06 Flytt PIN-sjekk til Keypad-biblioteket
2025-11-13 Lagt til BME280 bibliotek
    Utfyllende bibliotek forka fra Git.
2025-11-13 Lagt til mer
2025-11-13 Lagt til README
2025-11-13 Readme
2025-11-13 Lagt til nytt RFID-bibliotek + endret navn
2025-11-14 Refaktorering
2025-11-14 Laget mappe til eksempelprosjekter
2025-11-14 Lagt til TMP102 bibliotek
2025-11-14 Slettet mappe
2025-11-14 Lagt til riktig BME280 bibliotek
2025-11-14 Lagt til prosjekt gjennom PIO (platformio)
2025-11-14 Funker fjell!
2025-11-14 Tester litt
2025-11-14 Test!
2025-11-17 Lagt til NeoPixel
2025-11-17 Endret README
2025-11-17 Lagt til eksempler på debounce
2025-11-17 Lagt til LCD
2025-11-17 Refaktorering + lagt til flere eksempler fra Canvas
2025-11-17 Lagt til metode, step-by-step
2025-11-17 METODE.md
2025-11-18 Lagt til nytt prosjekt m/depedencies
2025-11-18 Fikset README
2025-11-18 Lagt til AdafruitGFX
2025-11-18 Lagt til flere biblioteker
2025-11-18 Lagt til Piezo m/alt du kan øsnske deg;)
2025-11-18 Lagt et miniprosjekt. Transistor m/LED
2025-11-18 Lagt til fungerende kode for RFID-leser m/autentisering
2025-11-18 Opprettet prosjekt for keypad
2025-11-18 Lagt til eksempler med LCD 16x2 skjerm
2025-11-18 .gitignore + refaktorering
2025-11-18 Refaktorering igjen
2025-11-18 Lagt til korrekt(?) mapping til keypad
2025-11-18 Keypad changes
2025-11-19 Lagt til ferdig prosjekt med keypad og inntasting av godkjent/ikke-godkjent kode
2025-11-19 Forsøker demovideo i README
2025-11-19 Tester mer rundt demovideo
2025-11-19 Lastet opp egen shorts-video på YouTube for demonstrasjon av keypad
2025-11-19 Lagt til demovideo av RFID-leser
2025-11-19 Lagt til demovideo av LCD med LDR
2025-11-19 Opprettet prosjekt for RFID-leser og keypad med 2FA
2025-11-19 Laget prosjekt med keypad med inntasting av kode mot LCD-skjerm + lastet opp demovideo
2025-11-19 Fikset URL
2025-11-19 Kommentert kode + småendringer for lesbarhet
2025-11-20 Lagt til SparkFun_ENS160 og fjernet Adafruit
2025-11-20 Lagt til riktig ENS160
2025-11-20 Fikset include
2025-11-20 Lagt til nytt prosjekt med Adafruit BME280. Ikke ferdig, men må reboote PC.
2025-11-20 Endret pins på rader og kolonner
2025-11-20 Lagt til bibliotek i keypad_LCD
2025-11-20 Oppdatert platformio.ini
2025-11-20 Fikset liten feil
2025-11-20 Lagt til kommentar. Uferdig delprosjekt
2025-11-20 Lagt til en haug av eksempelkode for inspirasjon
2025-11-20 Fiks fiks
2025-11-20 Fiks fiks igjen?
2025-11-20 Lagt til knapp for vinter/sommer-modus
2025-11-20 Slettet bibliotek
2025-11-21 Lagt til Adafruit Neopixel
2025-11-21 Lagt til PIR som styrer servomotor
2025-11-22 NeoPixel m/Ultrasonic sensor
2025-11-22 Fungerende PIR m/styring av servo
2025-11-22 SoilMoisture m/vannpumpe
2025-11-22 Lagt til I2C-scanner
2025-11-22 Formatering av all koden
2025-11-22 Satt meg godt inn i og kommentert kode med enum States
2025-11-22 Fixfix
2025-11-22 Lagt til eksempel med constrain
2025-11-22 Lagt til EMA-filter for å redusere støy fra analogRead
2025-11-23 Lagt til oppsummering i .pdf fil
2025-11-23 Lagt inn mappe med alle forelesningene
2025-11-23 Lagt til nyttig nettside i README
2025-11-24 Eksamen ferdig
2025-11-24 Slettet duplikat
2026-03-25 Add personal GitHub section to README
2026-03-25 Enhance README with Arduino project guidelines
    Added a step-by-step guide for Arduino projects, including useful websites and overall strategy for implementation.

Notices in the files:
parts and their libraries:
SparkFun-Aesthetics: Licensing: Creative Commons ShareAlike 4.0 International - https://creativecommons.org/licenses/by-sa/4.0
SparkFun-Aesthetics: Released under the Creative Commons Attribution Share-Alike 4.0 License
SparkFun-Aesthetics: https://creativecommons.org/licenses/by-sa/4.0
